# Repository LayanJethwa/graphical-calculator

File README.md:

## Graphical calculator ##

This design is for a graphical calculator that I am making, which will be able to plot graphs on a screen provided in human-readable infix notation.

I decided to make this as a fun maths-based project for my Computer Science NEA.

## Introduction ##

Graphical calculators and software are widely used in advanced mathematics. They are an easy way to visualise and analyse graphs and are useful in a classroom setting as well as to verify solutions to problems. Free digital softwares such as Desmos and Geogebra are used extensively, but they work best on computers, and it is not desirable to have them on phones either in a lesson. Physical graphical calculators are therefore used, created by companies such as Casio and Texas Instruments.

However, these physical calculators are very expensive. The Casio fx-CG50, one of the leading devices in the field, costs £140 from the manufacturer. These calculators are very good, with a multitude of features, but a lot of these features are very rarely used, adding to the price point unnecessarily. Additionally, these calculators function as scientific calculators as well, but people that own them generally also own a scientific calculator anyway that they use mainly for calculations.

I aim to create a physical calculator that is only for plotting graphs. This will be less costly to build and produce, and I will be able to tailor it to the end user. The hardware will be specialised, having a screen with a higher resolution than the CG50, and I will 3D print parts specifically for ergonomics.

## Features ##

- Explicitly defined graphs
    - Polynomials
    - Radicals
    - Exponentials
    - Reciprocals
    - Logarithmic graphs
    - Trigonometric graphs (sin, cos, tan and reciprocals)
    - Parametric graphs
    - Differential equations
    - Indefinite integrals
    - Combinations of the above
    - x = f(y) graphs
- Implicitly defined graphs
    - Circles
    - Ellipses
    - Parabolas
    - Horizontal parabolas
    - Hyperbolas
    - Multiple graphs simultaneously
- Graph manipulation
    - Pan
    - Zoom
    - View window
        - Axis bounds
        - Axis scaling
    - Graph colouring
- Buttons
    - Golden button
    - Degrees-radians ~~rocker switch~~ toggle switch
    - Zoom ~~momentary toggle switch~~ tactile switches
- Other features
    - Auto power-off

## Demo ##

You can see a software demo at the website: https://layanjethwa.github.io/graphical-calculator/code/build/web/

Currently it is not complete and I have only implemented methods for a few functions. As they will be triggered by physical switches on the calculator, they are triggered by keys currently:

| Keyboard key |  Calculator function  |
|:-----|------:|
| SHIFT + =  | + (addition) |
| SHIFT + 9   |  ( (left bracket)  |
| SHIFT + 0   | ) (right bracket) |
| SHIFT + 8   | * (multiplication) |
| q   | squared |
| w   | cubed |
| x   | variable letter x |
| /   | divide |
| p   | pi |
| l   | log |
| s   | sin |
| c   | cos |
| t   | tan |
| r   | csc |
| y   | sec |
| u   | cot |

The syntax of the log function is [base]log([value]), e.g. 2log(x) means log base 2 of x. Implicit multiplication is not currently defined for all functions.

You can use the arrow keys to pan around the graph, n to zoom in, and m to zoom out. When you enter the function, press enter to confirm, and then enter again to go to the graph page. You can also use the arrow keys on the input page to add more graphs to the display.

## Hardware ##

The PCB will be shaped like the calculator, and the switches for the buttons will be mounted to it directly. It will have connectors for the screen, CPU, and battery as well. 

The CPU I will be using is the Raspberry Pi Zero 2 W. It is 65mm x 30mm, so fairly small and will fit nicely in the calculator. It has 512 MB of RAM, and a clock speed of 1GHz, so it will not be able to handle more intensive computations. It has WiFi and Bluetooth connectivity, although I am not planning to use them, as well as a USB 2.0 port, a microSD card slot, a mini HDMI port, and a 40 pin I/O header. I will have to install an operating system on it, probably Raspbian, to run Python code.

The screen I have decided to use is a 3.5 inch LCD screen, intended for a display for a Raspberry Pi. It has a 320x480 pixel resolution, and also features resistive touch control, though I probably will not be utilizing that feature of it. The resolution is higher than the Casio fx-CG50, one of the leading graphical calculators, so it should be more than enough for my purposes. The screen is £24 directly from the manufacturer. The screen connects via ~~HDMI~~ TFT, and is powered by a micro USB connection.

I have decided to use tactile switches with attached shafts, which, as mentioned, will be soldered directly to the PCB. I plan on using the Omron B3F-1050 switches, which I can get from DigiKey, at around 12.5p each for the number I will require. They have dimensions of 6 x 6 mm with a height of 7.3 mm, which should be suitable for my purposes. I can buy keycaps for these switches, or 3D print them myself. I found many sites selling caps - there are some round ones on AliExpress for £2.79 per 100 caps, and also some square ones for £2.47 per 50 caps. I also found a model that I can 3D print, although this is for the larger 12x12x7.3 mm switches, but I can scale it down.

## Pictures ##

## BOM ##

|Part name|Quantity needed|Lot|Price|Link|
|-|-|-|-|-|
|PCB|1|5|$16.77|https://cart.jlcpcb.com/shopcart/cart/	|
|Raspberry Pi Zero 2W|1|1|$16.25|https://www.aliexpress.com/item/1005008147614202.html|
|Osoyoo 3.5in TFT LCD screen|1|1|$33.32|https://www.aliexpress.com/i/1005006494047405.html	|
|LiPo flat battery 5V 9000mAh|1|1|$11.52|https://www.aliexpress.com/item/1005005621203243.html|
|Omron B3F-1050|40|100|$16.95|https://www.aliexpress.com/item/4000012348941.html|
|JS2011CQN|1|1|$16.77|https://www.mouser.co.uk/ProductDetail/611-JS102011CQN|
|DO-35 1N4148|40|100|$1.02|https://www.aliexpress.com/item/1005004103990376.html|

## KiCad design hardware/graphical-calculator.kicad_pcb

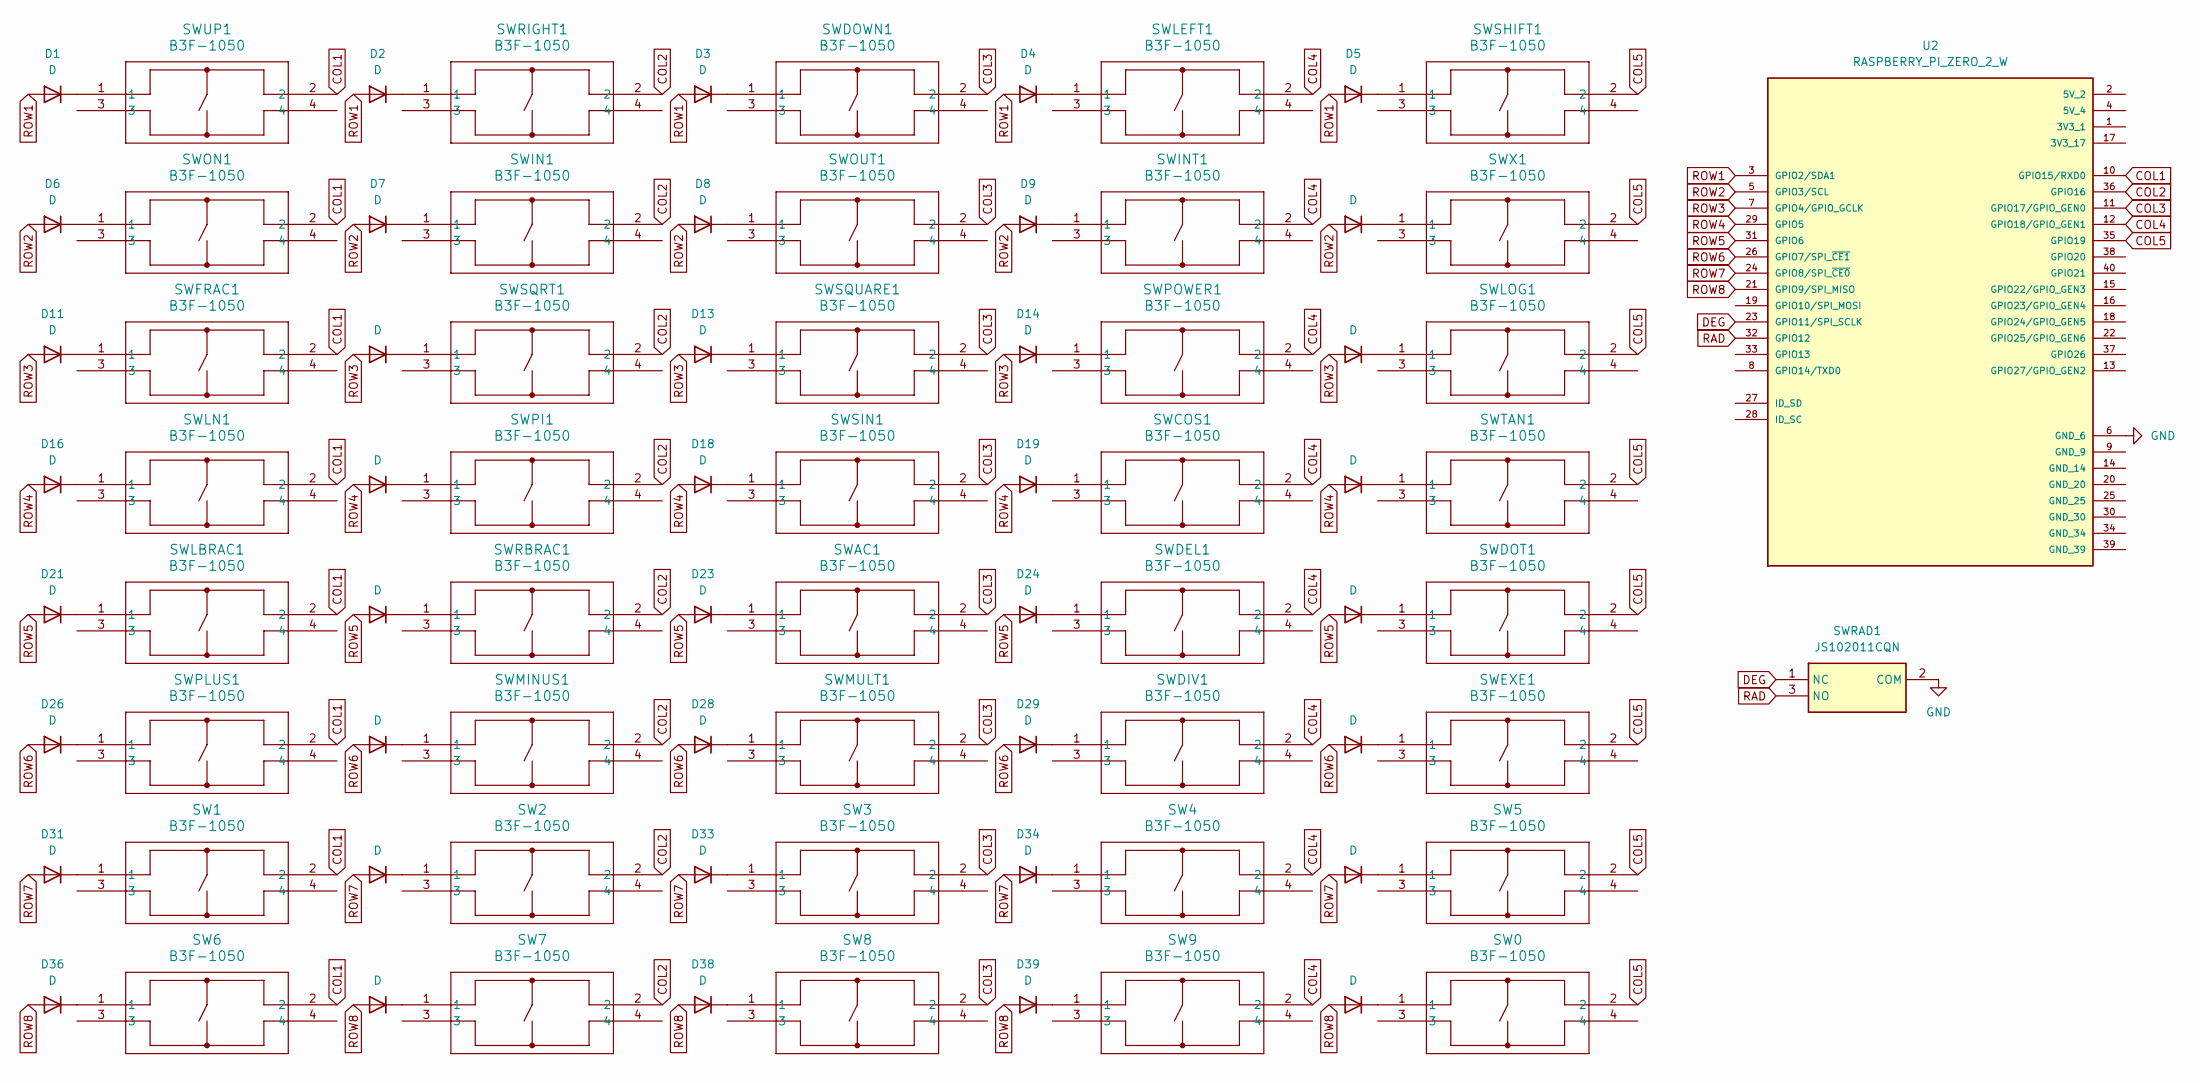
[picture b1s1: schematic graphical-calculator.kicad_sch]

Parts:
D1, D2, D3, D4, D5, D6, D7, D8, D9, D10, D11, D12, D13, D14, D15, D16, D17, D18, D19, D20, D21, D22, D23, D24, D25, D26, D27, D28, D29, D30, D31, D32, D33, D34, D35, D36, D37, D38, D39, D40: D; DIOAD1300W80L670D310
SW0, SW1, SW2, SW3, SW4, SW5, SW6, SW7, SW8, SW9: B3F-1050; SW_B3F-1050_OMR
SWAC1: B3F-1050; SW_B3F-1050_OMR
SWCOS1: B3F-1050; SW_B3F-1050_OMR
SWDEL1: B3F-1050; SW_B3F-1050_OMR
SWDIV1: B3F-1050; SW_B3F-1050_OMR
SWDOT1: B3F-1050; SW_B3F-1050_OMR
SWDOWN1: B3F-1050; SW_B3F-1050_OMR
SWEXE1: B3F-1050; SW_B3F-1050_OMR
SWFRAC1: B3F-1050; SW_B3F-1050_OMR
SWIN1: B3F-1050; SW_B3F-1050_OMR
SWINT1: B3F-1050; SW_B3F-1050_OMR
SWLBRAC1: B3F-1050; SW_B3F-1050_OMR
SWLEFT1: B3F-1050; SW_B3F-1050_OMR
SWLN1: B3F-1050; SW_B3F-1050_OMR
SWLOG1: B3F-1050; SW_B3F-1050_OMR
SWMINUS1: B3F-1050; SW_B3F-1050_OMR
SWMULT1: B3F-1050; SW_B3F-1050_OMR
SWON1: B3F-1050; SW_B3F-1050_OMR
SWOUT1: B3F-1050; SW_B3F-1050_OMR
SWPI1: B3F-1050; SW_B3F-1050_OMR
SWPLUS1: B3F-1050; SW_B3F-1050_OMR
SWPOWER1: B3F-1050; SW_B3F-1050_OMR
SWRAD1: JS102011CQN; Manufacturer_Part_Number JS102011CQN; Mouser Part Number 611-JS102011CQN
SWRBRAC1: B3F-1050; SW_B3F-1050_OMR
SWRIGHT1: B3F-1050; SW_B3F-1050_OMR
SWSHIFT1: B3F-1050; SW_B3F-1050_OMR
SWSIN1: B3F-1050; SW_B3F-1050_OMR
SWSQRT1: B3F-1050; SW_B3F-1050_OMR
SWSQUARE1: B3F-1050; SW_B3F-1050_OMR
SWTAN1: B3F-1050; SW_B3F-1050_OMR
SWUP1: B3F-1050; SW_B3F-1050_OMR
SWX1: B3F-1050; SW_B3F-1050_OMR
U2: RASPBERRY_PI_ZERO_2_W; MODULE_RASPBERRY_PI_ZERO_2_W; PARTREV April 2024

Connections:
COL1: SW1.2, SW6.2, SWFRAC1.2, SWLBRAC1.2, SWLN1.2, SWON1.2, SWPLUS1.2, SWUP1.2, U2.10 (GPIO15/RXD0)
COL2: SW2.2, SW7.2, SWIN1.2, SWMINUS1.2, SWPI1.2, SWRBRAC1.2, SWRIGHT1.2, SWSQRT1.2, U2.36 (GPIO16)
COL3: SW3.2, SW8.2, SWAC1.2, SWDOWN1.2, SWMULT1.2, SWOUT1.2, SWSIN1.2, SWSQUARE1.2, U2.11 (GPIO17/GPIO_GEN0)
COL4: SW4.2, SW9.2, SWCOS1.2, SWDEL1.2, SWDIV1.2, SWINT1.2, SWLEFT1.2, SWPOWER1.2, U2.12 (GPIO18/GPIO_GEN1)
COL5: SW0.2, SW5.2, SWDOT1.2, SWEXE1.2, SWLOG1.2, SWSHIFT1.2, SWTAN1.2, SWX1.2, U2.35 (GPIO19)
DEG: SWRAD1.1 (NC), U2.23 (GPIO11/SPI_SCLK)
GND: SWRAD1.2 (COM), U2.6 (GND_6)
unnamed: D1.1 (K), SWUP1.1
unnamed: D2.1 (K), SWRIGHT1.1
unnamed: D3.1 (K), SWDOWN1.1
unnamed: D4.1 (K), SWLEFT1.1
unnamed: D5.1 (K), SWSHIFT1.1
unnamed: D6.1 (K), SWON1.1
unnamed: D7.1 (K), SWIN1.1
unnamed: D8.1 (K), SWOUT1.1
unnamed: D9.1 (K), SWINT1.1
unnamed: D10.1 (K), SWX1.1
unnamed: D11.1 (K), SWFRAC1.1
unnamed: D12.1 (K), SWSQRT1.1
unnamed: D13.1 (K), SWSQUARE1.1
unnamed: D14.1 (K), SWPOWER1.1
unnamed: D15.1 (K), SWLOG1.1
unnamed: D16.1 (K), SWLN1.1
unnamed: D17.1 (K), SWPI1.1
unnamed: D18.1 (K), SWSIN1.1
unnamed: D19.1 (K), SWCOS1.1
unnamed: D20.1 (K), SWTAN1.1
unnamed: D21.1 (K), SWLBRAC1.1
unnamed: D22.1 (K), SWRBRAC1.1
unnamed: D23.1 (K), SWAC1.1
unnamed: D24.1 (K), SWDEL1.1
unnamed: D25.1 (K), SWDOT1.1
unnamed: D26.1 (K), SWPLUS1.1
unnamed: D27.1 (K), SWMINUS1.1
unnamed: D28.1 (K), SWMULT1.1
unnamed: D29.1 (K), SWDIV1.1
unnamed: D30.1 (K), SWEXE1.1
unnamed: D31.1 (K), SW1.1
unnamed: D32.1 (K), SW2.1
unnamed: D33.1 (K), SW3.1
unnamed: D34.1 (K), SW4.1
unnamed: D35.1 (K), SW5.1
unnamed: D36.1 (K), SW6.1
unnamed: D37.1 (K), SW7.1
unnamed: D38.1 (K), SW8.1
unnamed: D39.1 (K), SW9.1
unnamed: D40.1 (K), SW0.1
RAD: SWRAD1.3 (NO), U2.32 (GPIO12)
ROW1: D1.2 (A), D2.2 (A), D3.2 (A), D4.2 (A), D5.2 (A), U2.3 (GPIO2/SDA1)
ROW2: D6.2 (A), D7.2 (A), D8.2 (A), D9.2 (A), D10.2 (A), U2.5 (GPIO3/SCL)
ROW3: D11.2 (A), D12.2 (A), D13.2 (A), D14.2 (A), D15.2 (A), U2.7 (GPIO4/GPIO_GCLK)
ROW4: D16.2 (A), D17.2 (A), D18.2 (A), D19.2 (A), D20.2 (A), U2.29 (GPIO5)
ROW5: D21.2 (A), D22.2 (A), D23.2 (A), D24.2 (A), D25.2 (A), U2.31 (GPIO6)
ROW6: D26.2 (A), D27.2 (A), D28.2 (A), D29.2 (A), D30.2 (A), U2.26 (GPIO7/SPI_~CE1)
ROW7: D31.2 (A), D32.2 (A), D33.2 (A), D34.2 (A), D35.2 (A), U2.24 (GPIO8/SPI_~CE0)
ROW8: D36.2 (A), D37.2 (A), D38.2 (A), D39.2 (A), D40.2 (A), U2.21 (GPIO9/SPI_MISO)

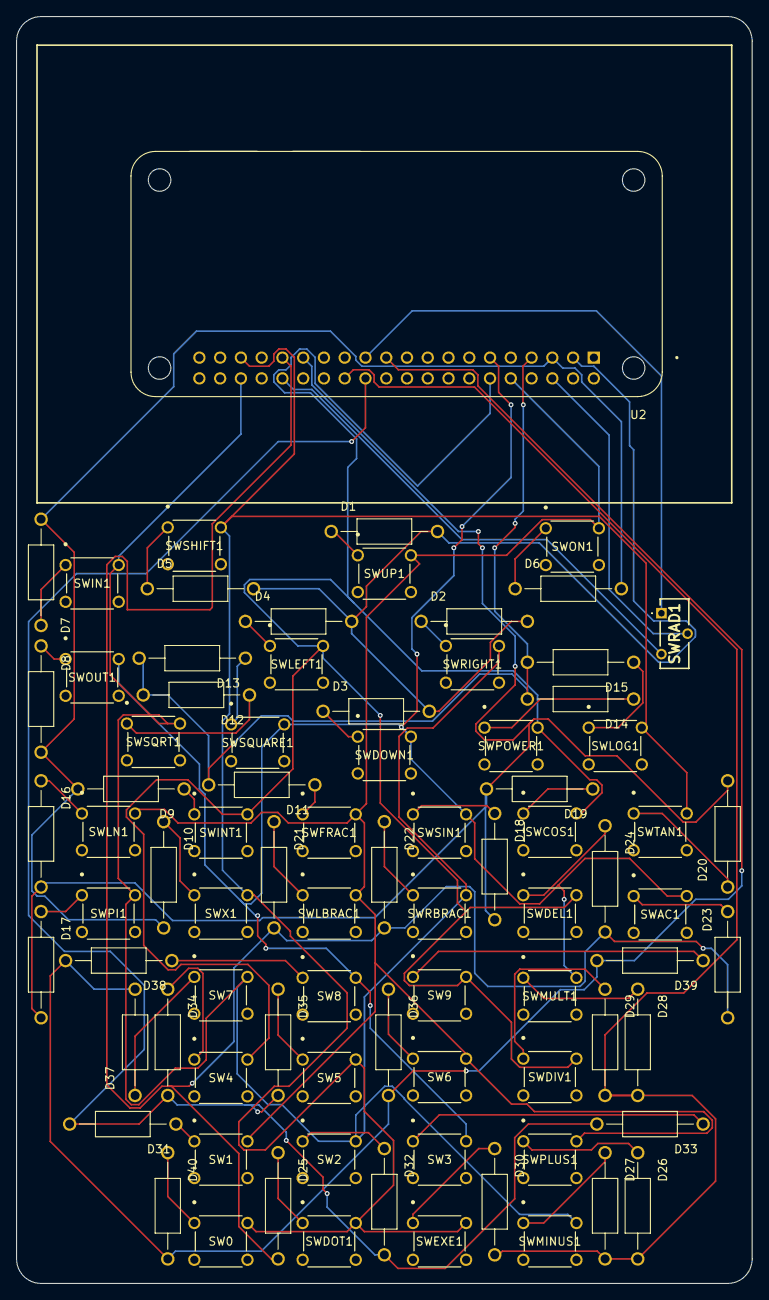
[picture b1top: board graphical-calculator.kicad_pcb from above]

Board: 2 copper layers, 90.0 x 155.0 mm, 82 parts (0 on the bottom side), 56 nets.

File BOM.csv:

Part name	Quantity needed	Lot	Price (USD)	Link	Notes
Raspberry Pi Zero 2W	1	1	$16.25	https://www.aliexpress.com/item/1005008147614202.html	
Osoyoo 3.5in DSI LCD screen	1	1	$33.32	https://www.aliexpress.com/i/1005006494047405.html	
LiPo flat battery 5V 9000mAh	1	1	$11.52	https://www.aliexpress.com/item/1005006611580965.html	
Omron B3F-1050	40	100	$16.95	https://www.aliexpress.com/item/1005006611580965.html	
DO-35 1N4148	40	100	$1.02	https://www.aliexpress.com/item/1005004103990376.html	
JS2011CQN	1	1	$16.77	https://www.mouser.co.uk/ProductDetail/611-JS102011CQN	£12 shipping fees - I will order some more items with my own money that I need to make the most of this
PCB	1	5	$15.18	https://cart.jlcpcb.com/shopcart/cart/

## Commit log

2025-06-09 Rename README.md to JOURNAL.md
2025-06-09 Rename Screenshot 2025-06-09 205337.png to images/09-06.png
2025-06-16 Rename Screenshot 2025-06-16 223827.png to 16-06.png
2025-06-16 Rename Objectives breakdown 16-06.docx to documents/Objectives breakdown 16-06.docx
2025-06-24 Rename Screenshot 2025-06-24 124429.png to 23-06-1.png
2025-06-24 Rename Screenshot 2025-06-24 124650.png to 23-06-2.png
2025-07-01 Rename Objectives breakdown 16-06.docx to Objectives breakdown.docx
2025-07-01 Rename Links 16-06.docx to Links.docx
2025-07-01 Rename Screenshot 2025-07-01 085953.png to 30-06.png
2025-07-02 Rename Screenshot 2025-07-02 201819.png to 02-07-1.png
2025-07-02 Rename 02-07-1.png to 02-07-2.png
2025-07-02 Rename Screenshot 2025-07-02 201828.png to 02-07-1.png
2025-07-04 Rename Screenshot 2025-07-04 201539.png to 03-07-1.png
2025-07-04 Rename Screenshot 2025-07-04 201550.png to 03-07-2.png
2025-07-21 journal entry, updated documents
2025-07-22 created parser for polynomials, currently implements +,-,/,*,(),^,x
2025-07-22 renamed numbers to operands because 🤓☝️
2025-07-22 yay parser and evaluator now working
2025-07-23 added axis labels
2025-07-23 added an input display, to-do list, and integrated input and graph display in main file
2025-07-23 update journal and add spacing
2025-07-23 update journal with images
2025-07-23 update todo
2025-07-24 allowed negative numbers and decimals as inputs, added move and zoom functions
2025-07-24 added constants, reciprocal, logarithmic, trigonometric graphs and asymptotes
2025-07-24 added view window, update journal and to-do
2025-07-27 created schematic and pcb
2025-07-30 update pcb and 3d model
2025-07-30 update bom
2025-07-31 redo board with matrix, tht, cad with screen
2025-08-06 updated render, keycaps and pins
2025-08-06 update render image
2025-09-10 update pcb
2025-10-01 build with pygbag
2025-10-01 update readme with instructions for web app
2025-10-01 add more instructions in readme
2025-11-03 Rename JOURNAL.md to HIGHWAY_JOURNAL.md
2026-02-20 oop yay ig
2026-02-22 fetched code from rpi with separate folder for code that goes directly to hardware
2026-02-22 fractions centred now, font in rendering is dynamic instead of scaling down after
2026-02-22 added support for decimal points, unary negation, brackets, changed colours
2026-02-22 added implicit multiplication
2026-03-01 code fully completed
2026-03-01 create design folder
2026-03-01 recreate design.txt
2026-03-01 Added Calculator high-level overview.drawio
2026-03-01 Added Calculator high-level overview.drawio.png
2026-03-01 Added render_graphs.drawio
2026-03-01 Added render_graphs.drawio.png
2026-03-02 remove function safe_chr
2026-03-02 Added expression_tree.drawio
2026-03-02 exponent defined twice
2026-03-02 Added expression_tree.drawio.png
2026-03-02 Added Expression_tree evaluate.drawio
2026-03-03 Added Expression_tree evaluate.drawio.png
2026-03-03 Added Module overview.drawio
2026-03-03 Added Module overview.drawio.png
2026-03-03 comments
2026-03-04 Added Parser algorithm.drawio
2026-03-04 Added Parser algorithm.drawio.png
2026-03-04 Added file structure.drawio
2026-03-04 Added file structure.drawio.png
2026-03-18 lots of changes and comments
2026-03-29 complete nea
